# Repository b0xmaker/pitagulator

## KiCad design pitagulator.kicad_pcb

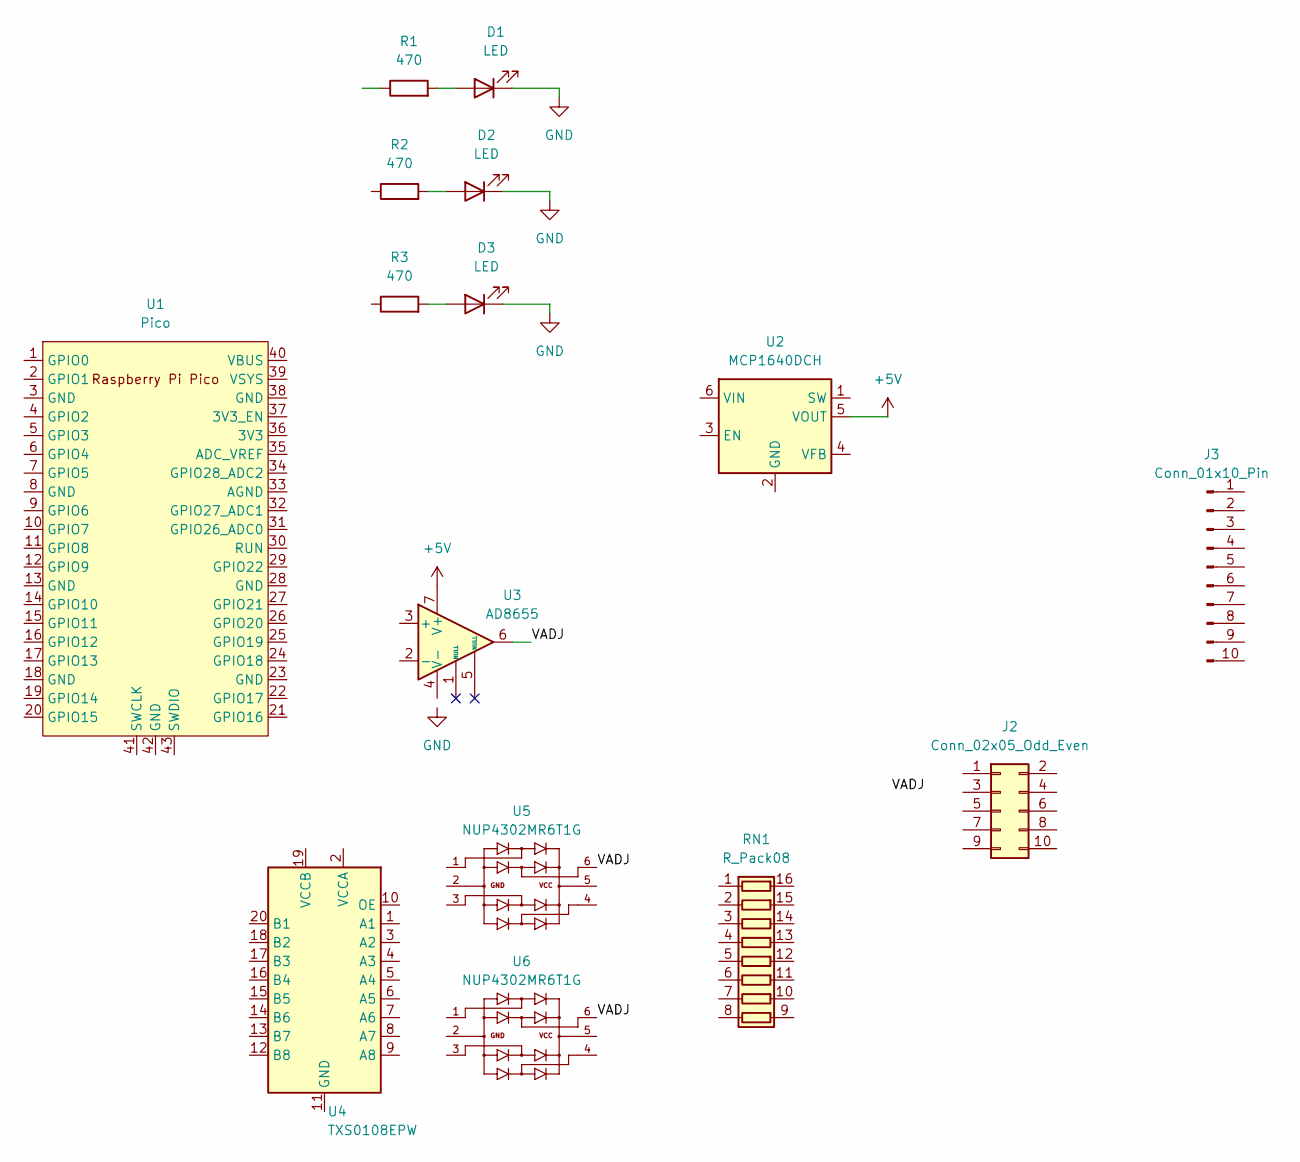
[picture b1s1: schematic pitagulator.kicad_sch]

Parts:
D1, D2, D3: LED; LED_0805_2012Metric_Pad1.15x1.40mm_HandSolder
J2: Conn_02x05_Odd_Even; PinHeader_2x05_P2.54mm_Vertical_SMD
J3: Conn_01x10_Pin; PinHeader_1x10_P2.54mm_Vertical
R1, R2, R3: 470; R_0805_2012Metric_Pad1.20x1.40mm_HandSolder
RN1: R_Pack08; SOIC-16W_5.3x10.2mm_P1.27mm
U1: Pico; RPi_Pico_SMD_TH
U2: MCP1640DCH; SOT-23-6
U3: AD8655; MSOP-8_3x3mm_P0.65mm
U4: TXS0108EPW; TSSOP-20_4.4x6.5mm_P0.65mm
U5, U6: NUP4302MR6T1G; TSOP-6_1.65x3.05mm_P0.95mm; PARTREV 12 JUN 2012

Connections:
+5V: U2.5 (VOUT), U3.7 (V+)
/VADJ: U3.6, U5.6, U6.6
GND: D1.1 (K), D2.1 (K), D3.1 (K)
unnamed: D1.2 (A), R1.2
unnamed: D2.2 (A), R2.2
unnamed: D3.2 (A), R3.2

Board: 2 copper layers, 15 parts (0 on the bottom side), 6 nets, no tracks yet.

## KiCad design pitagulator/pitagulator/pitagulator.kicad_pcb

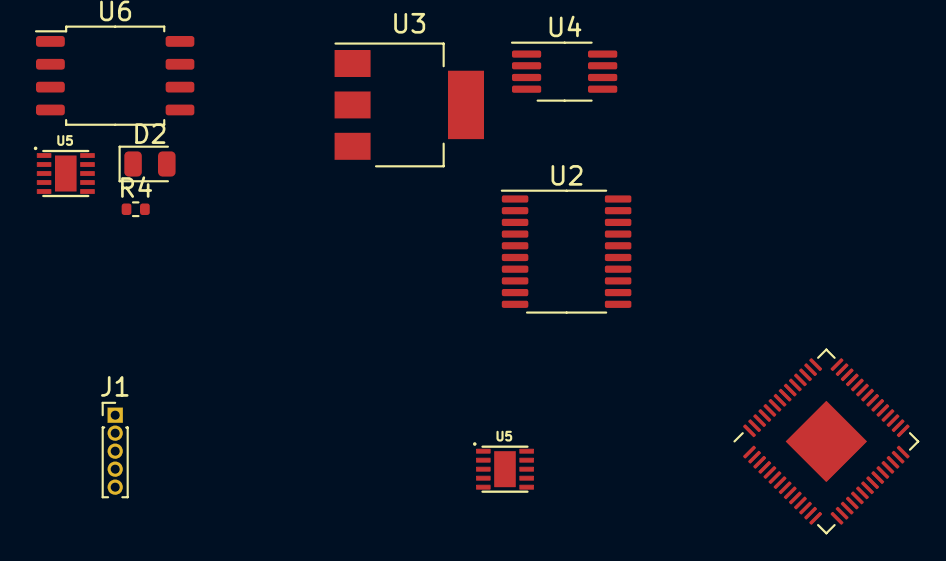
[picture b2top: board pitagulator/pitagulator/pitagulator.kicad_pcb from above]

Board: 2 copper layers, 10 parts (0 on the bottom side), 13 nets, no tracks yet.

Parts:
D2: LED; LED_0805_2012Metric
J1: Conn_01x05_Socket; PinHeader_1x05_P1.00mm_Vertical
R4: 100k; R_0402_1005Metric
U1: RP2040; QFN-56-1EP_7x7mm_P0.4mm_EP3.2x3.2mm
U2: TXS0108EPW; TSSOP-20_4.4x6.5mm_P0.65mm
U3: LD1117S33TR_SOT223; SOT-223-3_TabPin2
U4: MIC2025-2YMM; MSOP-8_3x3mm_P0.65mm
U5, U5#2: RT6150B-33GQW; SON50P250X250X80-11N
U6: W25Q128JVS; SOIC-8_5.23x5.23mm_P1.27mm

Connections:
3V3: U5.1 (VOUT), U5.10 (FB), U5#2.1 (VOUT)
CH0: J1.2, U1.2 (GPIO0)
CH1: J1.3, U1.3 (GPIO1)
CH2: J1.4, U1.4 (GPIO2)
CH3: J1.5, U1.5 (GPIO3)
CH23: R4.1, U1.35 (GPIO23), U5.7 (PS)
GND: D2.1 (K), J1.1, R4.2, U1.57 (GND), U5.3 (GND), U5.9 (GND), U5.11 (EXP), U5#2.3 (GND), U5#2.9 (GND), U5#2.11 (EXP)
unnamed: U5.5 (VIN), U5.8 (VINA)
unnamed: U1.23 (DVDD), U1.50 (DVDD)
unnamed: U1.1 (IOVDD), U1.10 (IOVDD), U1.22 (IOVDD), U1.33 (IOVDD), U1.42 (IOVDD), U1.49 (IOVDD)
unnamed: U4.6 (OUT), U4.8 (OUT)
unnamed: U5.4 (LX1), U5#2.4 (LX1)
unnamed: U5.2 (LX2), U5#2.2 (LX2)
